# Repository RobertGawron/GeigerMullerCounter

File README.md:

# GeigerMullerCounter

## Purpose

The Geiger–Müller counter is a simple, reliable tool designed to measure ionizing radiation. It is widely used in experiments, radiation detection, and environmental monitoring.

## Principle of Operation
When a high voltage (typically 380–420V) is applied to the Geiger–Müller tube, the tube does not conduct electricity under normal conditions. However, when a radiation particle interacts with the tube, it briefly conducts a current, producing a pulse. These pulses are counted by the detector, and the number of pulses in a given time interval (typically 20 seconds to 2.5 minutes) is proportional to the level of ionizing radiation.

## Final Version
Below is an image of the device (the green PCB in the center). Other components in the image are not relevant to this project, as they belong to the [Cosmic Ray Detector](https://github.com/RobertGawron/CosmicRayDetector), where the Geiger counter is used as a building block.

## System Architecture

The diagram shows the main components and how they interact. The component IDs in parentheses match those in the circuit diagram below, making it easier to understand the circuit.

Tools: PlantUML

## Hardware 

The circuit is shown below. For a full-size image, right-click and open it in a new tab.

Tools: KiCad (for PCB design).

More info can be fond in [here](Hardware/GeigerMullerCounter/README.md).

## Software

Data from the Geiger–Müller counter is collected and managed using the [HardwareDataLogger](https://github.com/RobertGawron/HardwareDataLogger), which is built around an STM32 microcontroller for data collection, display, and storage (via SD card), and an ESP8266 for WiFi communication.

Tools: C++, Python.

## Experiments Conducted

* [Measuring Nuclear Radiation of Potassium from Cigarette Ashes](https://robertgawron.blogspot.com/2015/07/measuring-radioactivity-of-potassium.html): Cigarette ashes are the burnt remains of tobacco leaves, which are rich in potassium. In natural environments, potassium contains the radioactive isotope potassium-40 (K-40), which contributes to the measured radiation levels.
* [Cosmic Ray Detector](https://github.com/RobertGawron/CosmicRayDetector): a device designed to detect high-energy particles, known as cosmic rays, that originate from outer space.
* [Trip to Śnieżka mountain to measure radioactivity levels](https://robertgawron.blogspot.com/2015/06/a-trip-with-geiger-counter-on-sniezka.html): mountains naturally have elevated radiation levels due to increased cosmic rays and radioactive minerals in the rocks. Additionally, near Śnieżka Mountain, a Cold War-era uranium mine in Kowary contributed to the region's historical radiation levels.

## Safety Hazards

**Warning: The device operates at high voltage (380–420V). Contact with the PCB or Geiger tube while powered can cause electric shocks, injuries, or even death. Do not touch any components while the device is powered on.**

## License
This project is licensed under the MIT License. See the [LICENSE](./LICENSE) file for details.

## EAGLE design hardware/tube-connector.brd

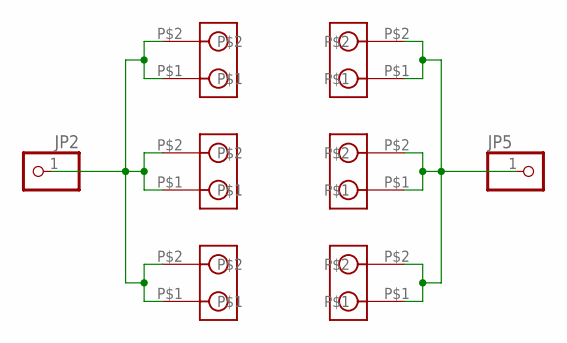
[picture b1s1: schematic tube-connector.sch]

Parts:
JP2, JP5: PINHD-1X1; 1X01
U$1, U$2, U$3, U$4, U$5, U$6: GM-CONNECTOR

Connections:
unnamed: JP2.1, U$1.P$1, U$1.P$2, U$2.P$1, U$2.P$2, U$3.P$1, U$3.P$2
unnamed: JP5.1, U$4.P$1, U$4.P$2, U$5.P$1, U$5.P$2, U$6.P$1, U$6.P$2

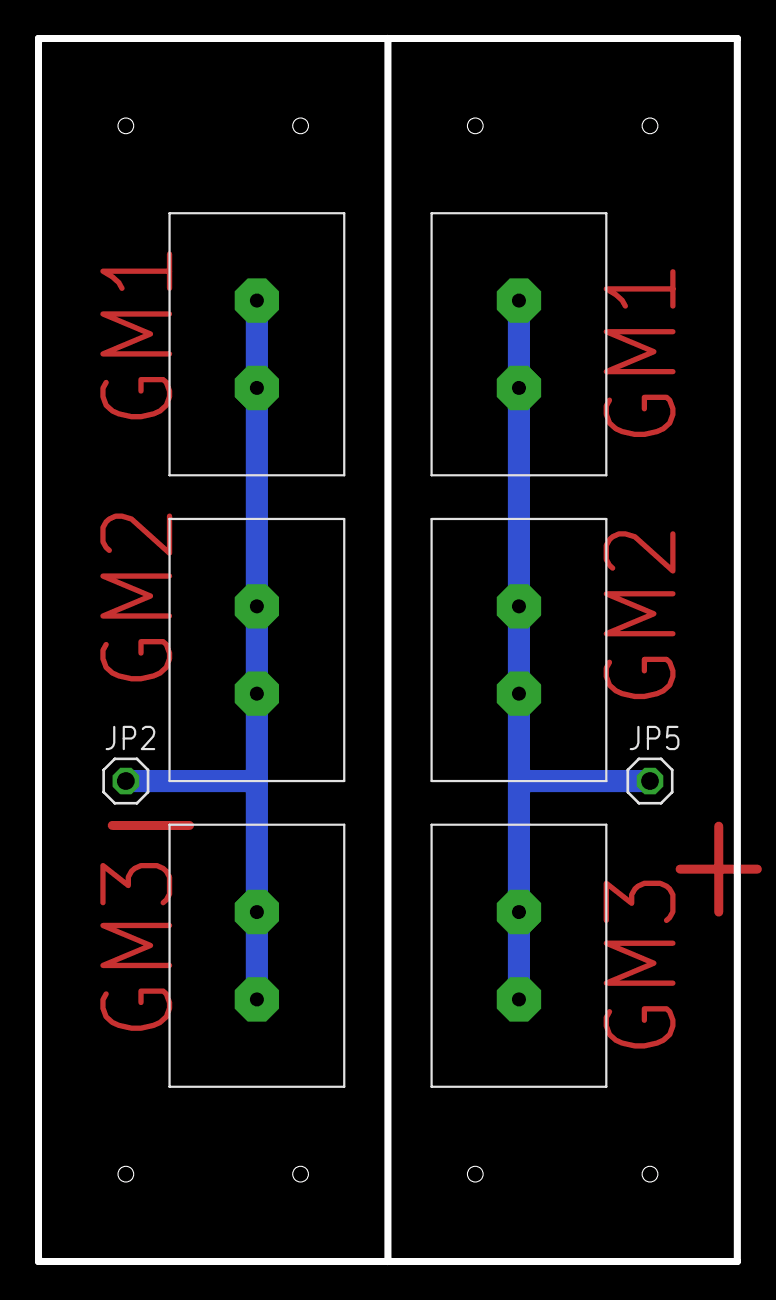
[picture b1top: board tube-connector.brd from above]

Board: 2 copper layers, 40.0 x 70.0 mm, 8 parts (0 on the bottom side), 2 nets.

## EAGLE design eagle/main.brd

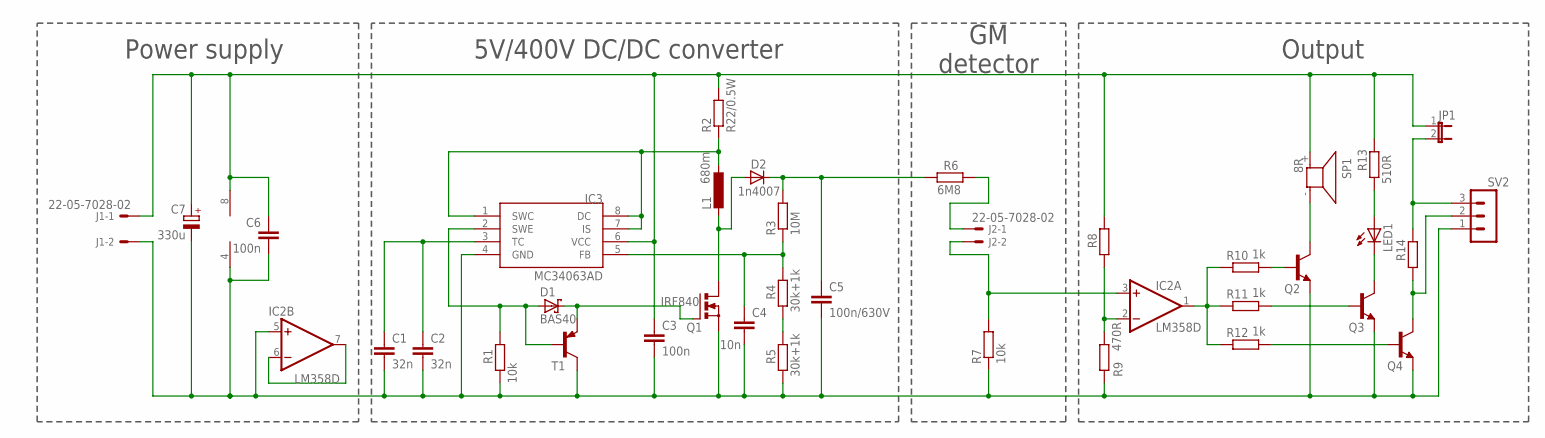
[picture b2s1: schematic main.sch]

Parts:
C1, C2: 32n; C0805
C3, C6: 100n; C0805
C4: 10n; C0805
C5: 100n/630V; C102-064X133
C7: 330u; D/7343-31R
D1: BAS40; SOT23
D2: 1n4007; DO41-10
IC2: LM358D; SO08
IC3: MC34063AD; SOIC8
J1, J2: 22-05-7028-02; 7395-02
JP1: JP1E; JP1
L1: 680m; 0207/5V
LED1: LEDSFH482; SFH482
Q1: IRF840; TO220BV
Q2, Q3, Q4: BC848ALT1SMD; SOT23
R1: 10k; R0805
R2: R22/0.5W; 0207/5V
R3: 10M; 0207/5V
R4, R5: 30k+1k; R0805
R6: 6M8; 0207/5V
R7: 10k; 0207/5V
R8: R-EU_R0805; R0805
R9: 470R; R0805
R10, R11, R12: 1k; M0805
R13: 510R; M0805
R14: R-EU_M0805; M0805
SP1: 8R; KSS1201
SV2: MA03-1
T1: BC807-40-PNP-SOT23-BEC; SOT23-BEC

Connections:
unnamed: Q4.1 (B), R12.2
unnamed: Q3.1 (B), R11.2
unnamed: LED1.K (C), Q3.3 (C)
unnamed: Q4.3 (C), R14.1, SV2.2
unnamed: C1.1, C2.1, IC3.3 (TC)
unnamed: LED1.A, R13.1
unnamed: IC3.1 (SWC), IC3.7 (IS), IC3.8 (DC), L1.1, R2.1
unnamed: IC2.1 (OUT), R10.1, R11.1, R12.1
unnamed: Q2.3 (C), SP1.- (2)
unnamed: Q2.1 (B), R10.2
unnamed: R4.1, R5.2
unnamed: C5.1, D2.C, R3.2, R6.1
unnamed: C4.1, IC3.5 (FB), R3.1, R4.2
unnamed: D1.1 (A), IC3.2 (SWE), R1.2, T1.B
unnamed: D2.A, L1.2, Q1.D
unnamed: D1.3 (C), Q1.G, T1.E
unnamed: IC2.3 (+IN), J2.2, R7.2
unnamed: J2.1, R6.2
unnamed: IC2.2 (-IN), R8.1, R9.2
unnamed: JP1.2, R14.2, SV2.3
unnamed: IC2.6 (-IN), IC2.7 (OUT)
V+: C3.1, C6.1, C7.+, IC2.8 (V+), IC3.6 (VCC), J1.1, JP1.1, R2.2, R8.2, R13.2, SP1.+ (1)
V-: C1.2, C2.2, C3.2, C4.2, C5.2, C6.2, C7.-, IC2.4 (V-), IC2.5 (+IN), IC3.4 (GND), J1.2, Q1.S, Q2.2 (E), Q3.2 (E), Q4.2 (E), R1.1, R5.1, R7.1, R9.1, SV2.1, T1.C

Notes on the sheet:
Power supply
5V/400V DC/DC converter
GM detector
Output

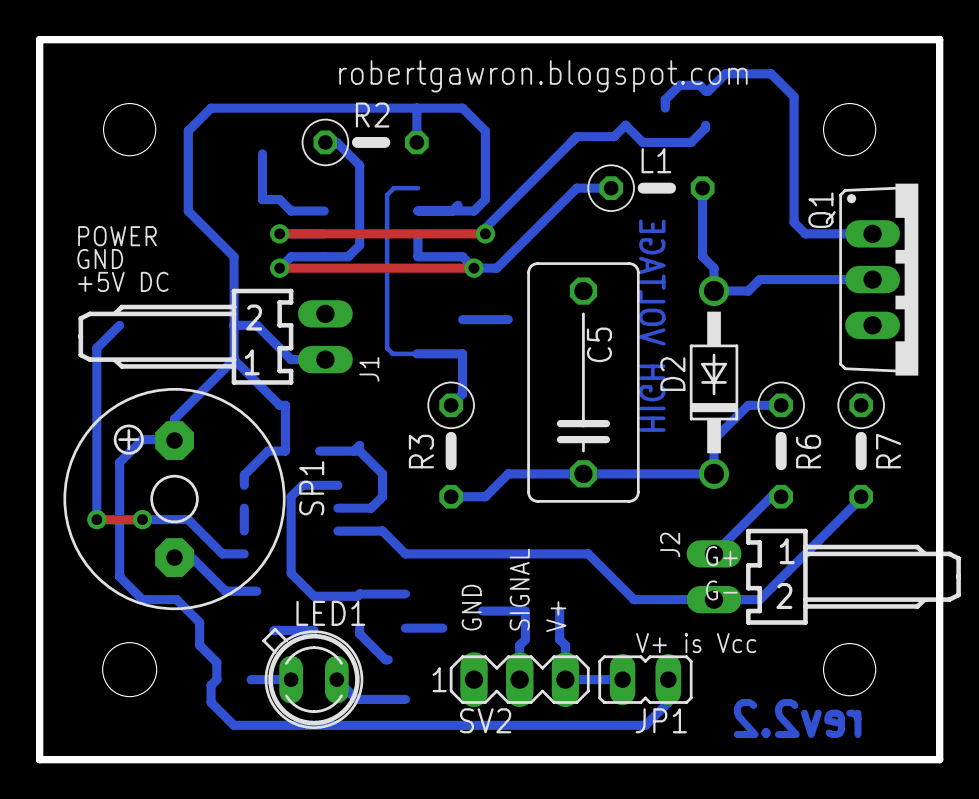
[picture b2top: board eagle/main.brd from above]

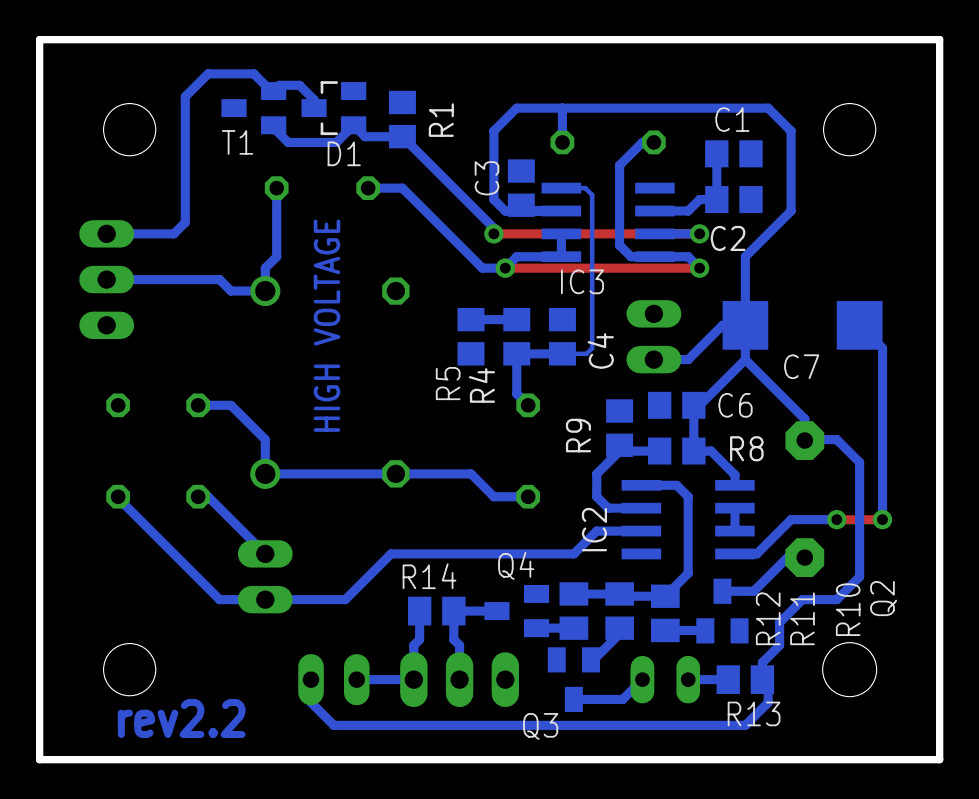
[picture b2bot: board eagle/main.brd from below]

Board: 2 copper layers, 50.0 x 40.0 mm, 37 parts (23 on the bottom side), 23 nets.

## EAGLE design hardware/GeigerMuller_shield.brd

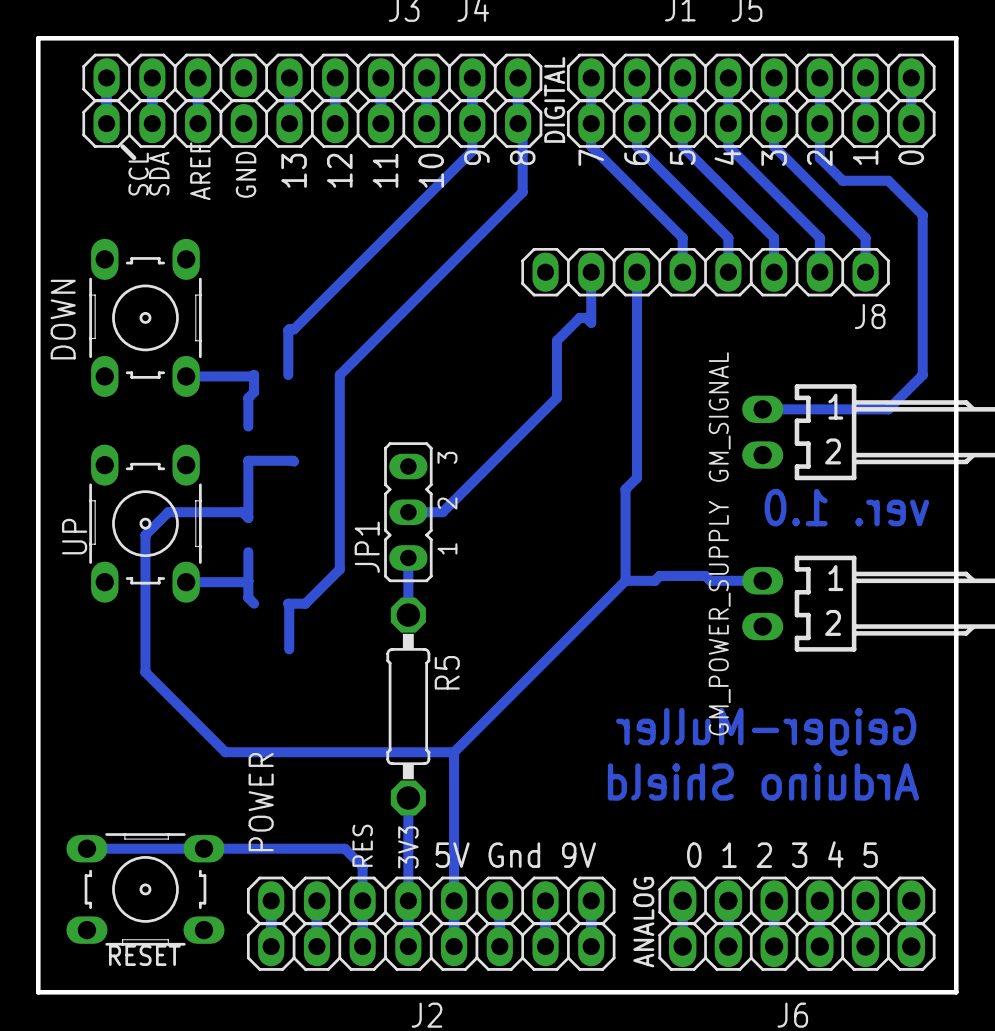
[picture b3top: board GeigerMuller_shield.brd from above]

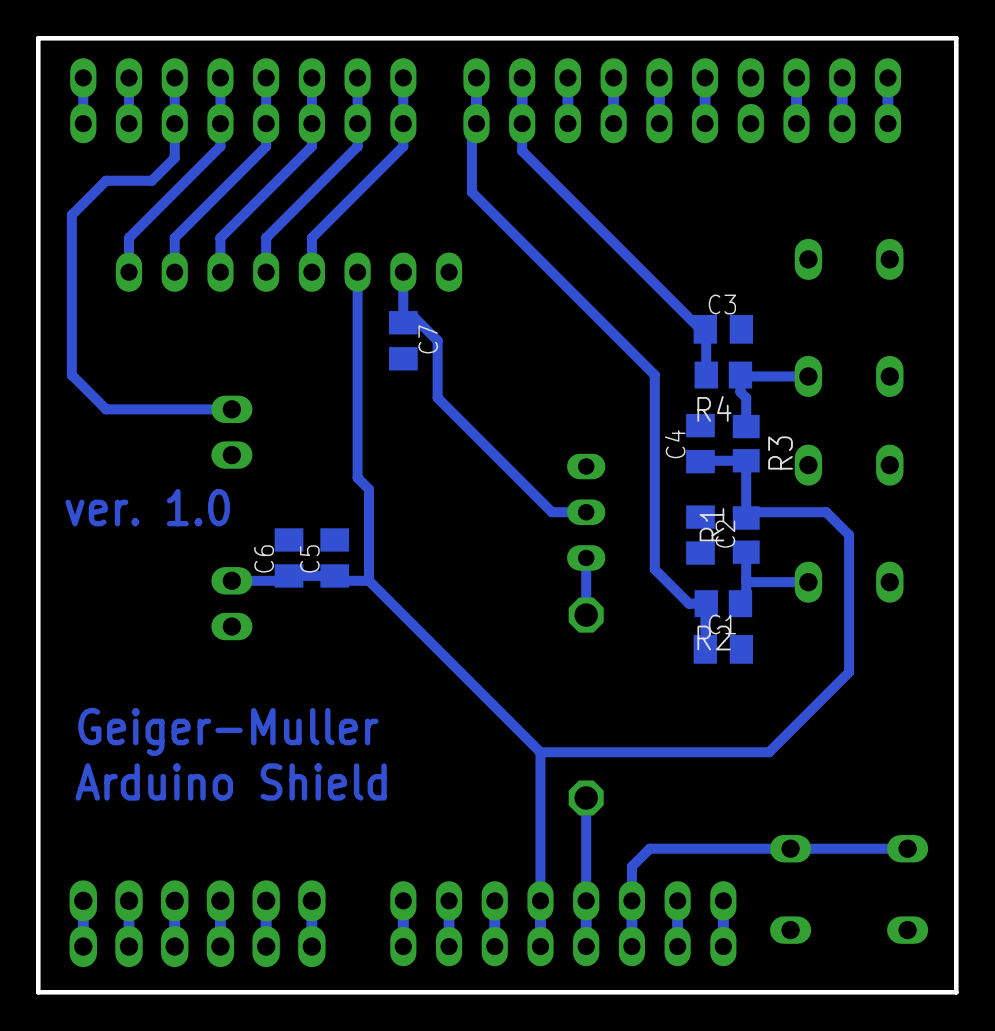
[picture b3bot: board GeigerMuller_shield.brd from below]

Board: 2 copper layers, 51.0 x 53.0 mm, 28 parts (11 on the bottom side), 34 nets.

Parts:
ANALOG: 1X06
C1, C3, C5, C6, C7: 10n; C0805K
C2, C4: 100n; C0805K
DOWN: B3F-10XX
GM_POWER_SUPPLY: 22-05-7028-02; 7395-02
GM_SIGNAL: 22-05-7028-02; 7395-02
J1, J2, J5, J8: 1X08-TH
J3, J4: 1X10-TH
J6: 1X06
JP1: JP2
POWER: 1X08-TH
R1, R3: 10k; R0805
R2, R4: 1k; R0805
R5: 220R; 0207/10
RESET: B3F-10XX
U$1: DISCLAIMER
UP: B3F-10XX

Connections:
3V3: J2.4, POWER.4, R5.2
+5V: C2.1, C4.1, C5.1, C6.1, GM_POWER_SUPPLY.1, J2.5, J8.6, POWER.5, R1.2, R3.2
+9V: J2.8, POWER.8
BUTTON_1: C1.1, J3.1, J4.1, R2.2
BUTTON_2: C3.1, J3.2, J4.2, R4.2
GM_SIGNAL: GM_SIGNAL.1, J1.3, J5.3
GND: C1.2, C2.2, C3.2, C4.2, C5.2, C6.2, C7.2, DOWN.4, GM_POWER_SUPPLY.2, GM_SIGNAL.2, J2.6, J2.7, J3.7, J4.7, J8.8, POWER.6, POWER.7, RESET.1, RESET.2, UP.4
LCD_BACKLIGHT: C7.1, J8.7, JP1.2
LCD_CS: J1.7, J5.7, J8.4
LCD_DC: J1.6, J5.6, J8.3
LCD_DIN: J1.5, J5.5, J8.2
LCD_RST: J1.8, J5.8, J8.5
LCD_SCLK: J1.4, J5.4, J8.1
unnamed: J3.6, J4.6
unnamed: J1.2, J5.2
unnamed: J3.4, J4.4
unnamed: J3.5, J4.5
unnamed: R1.1, R2.1, UP.2
unnamed: J1.1, J5.1
unnamed: J3.3, J4.3
unnamed: JP1.1, R5.1
unnamed: DOWN.2, R3.1, R4.1
unnamed: ANALOG.1, J6.1
unnamed: ANALOG.2, J6.2
unnamed: ANALOG.3, J6.3
unnamed: ANALOG.4, J6.4
unnamed: ANALOG.5, J6.5
unnamed: ANALOG.6, J6.6
unnamed: J2.2, POWER.2
unnamed: J2.1, POWER.1
unnamed: J3.9, J4.9
unnamed: J3.10, J4.10
unnamed: J3.8, J4.8
RESET: J2.3, POWER.3, RESET.3, RESET.4

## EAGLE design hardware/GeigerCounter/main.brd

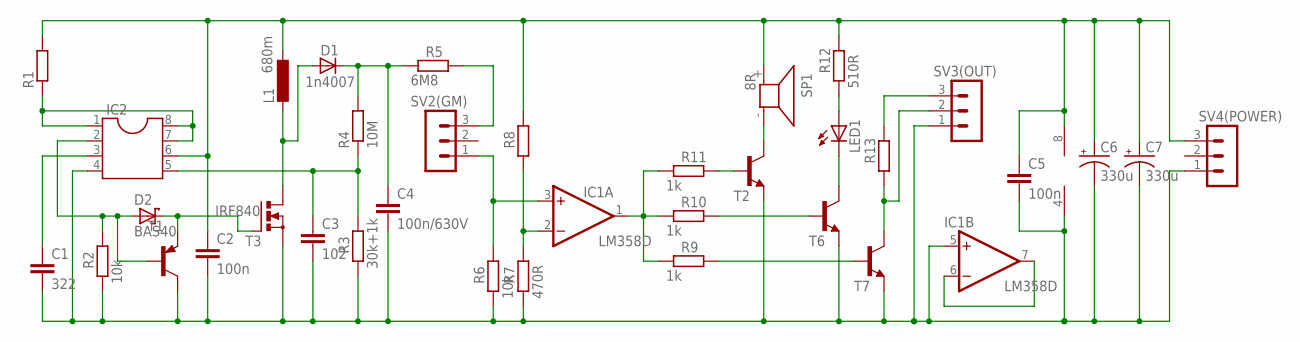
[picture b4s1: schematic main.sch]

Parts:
C1: 322; C050-025X075
C2, C5: 100n; C3216
C3: 102; C050-025X075
C4: 100n/630V; C102-064X133
C6, C7: 330u; A/3216-18W
D1: 1n4007; DO41-10
D2: BAS40; SOT23
IC1: LM358D; SO08
IC2: DIL8; DIL08
L1: 680m; 0207/5V
LED1: LEDSFH482; SFH482
R1, R8: R-EU_0207/5V; 0207/5V
R2, R6: 10k; 0207/5V
R3: 30k+1k; 0207/5V
R4: 10M; 0207/5V
R5: 6M8; 0207/12
R7: 470R; 0207/5V
R9, R10, R11: 1k; M1206
R12: 510R; M1206
R13: R-EU_M1206; M1206
SP1: 8R; KSS1201
SV2(GM), SV3(OUT), SV4(POWER): MA03-1
T1: BC807-40-PNP-SOT23-BEC; SOT23-BEC
T2, T6, T7: BC848ALT1SMD; SOT23
T3: IRF840; TO220BV

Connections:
unnamed: R9.2, T7.1 (B)
unnamed: R10.2, T6.1 (B)
unnamed: LED1.K (C), T6.3 (C)
unnamed: R13.1, SV3(OUT).2, T7.3 (C)
unnamed: C1.1, IC2.3
unnamed: LED1.A, R12.1
unnamed: IC1.1 (OUT), R9.1, R10.1, R11.1
unnamed: SP1.- (2), T2.3 (C)
unnamed: R11.2, T2.1 (B)
unnamed: IC2.1, IC2.7, IC2.8, R1.1
unnamed: C4.1, D1.C, R4.2, R5.1
unnamed: C3.1, IC2.5, R3.2, R4.1
unnamed: D2.1 (A), IC2.2, R2.2, T1.B
unnamed: D1.A, L1.2, T3.D
unnamed: D2.3 (C), T1.E, T3.G
unnamed: IC1.3 (+IN), R6.2, SV2(GM).1
unnamed: IC1.2 (-IN), R7.2, R8.1
unnamed: R5.2, SV2(GM).3
unnamed: R13.2, SV3(OUT).3
unnamed: IC1.6 (-IN), IC1.7 (OUT)
V+: C2.1, C5.1, C6.+, C7.+, IC1.8 (V+), IC2.6, L1.1, R1.2, R8.2, R12.2, SP1.+ (1), SV4(POWER).3
V-: C1.2, C2.2, C3.2, C4.2, C5.2, C6.-, C7.-, IC1.4 (V-), IC1.5 (+IN), IC2.4, R2.1, R3.1, R6.1, R7.1, SV3(OUT).1, SV4(POWER).1, T1.C, T2.2 (E), T3.S, T6.2 (E), T7.2 (E)

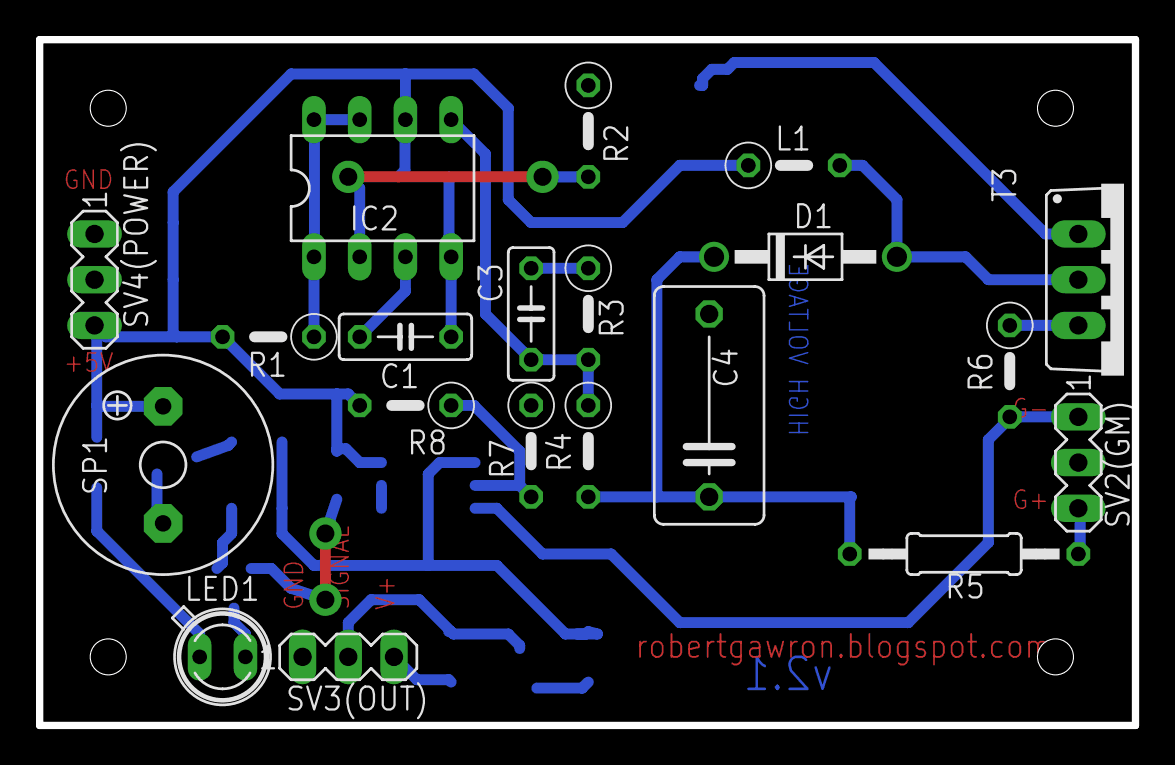
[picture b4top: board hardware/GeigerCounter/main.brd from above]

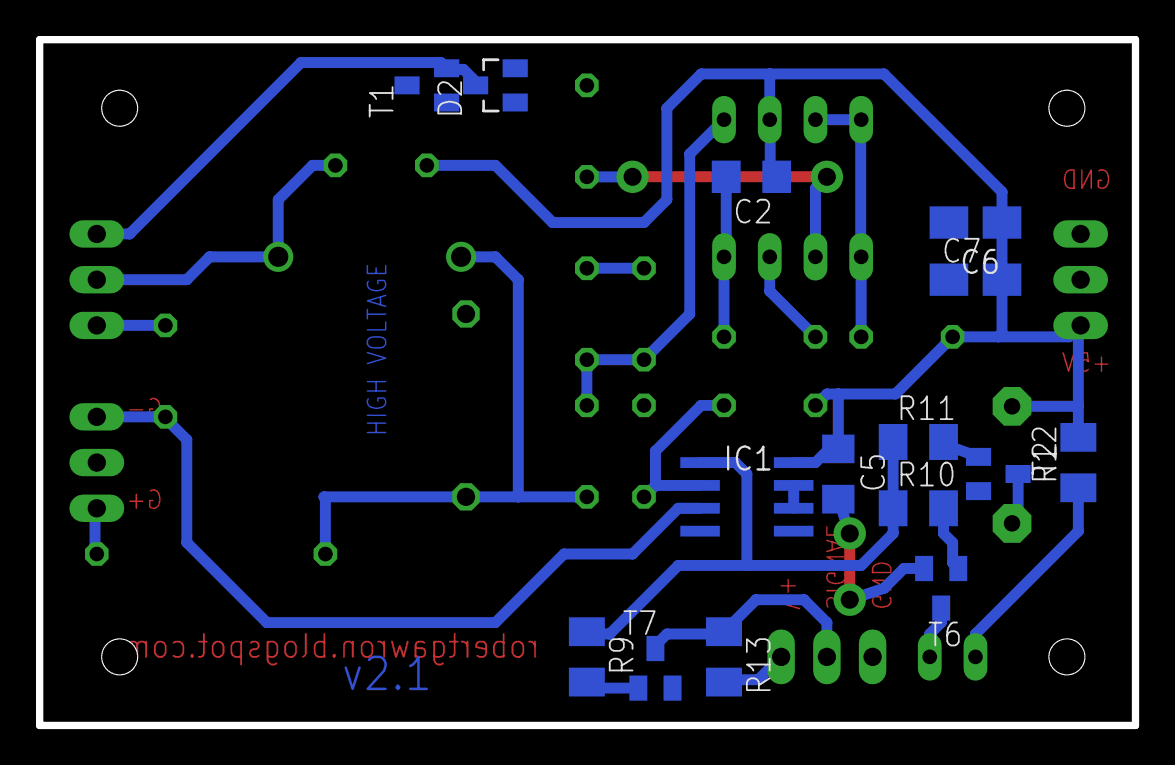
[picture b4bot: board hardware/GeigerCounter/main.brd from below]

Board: 2 copper layers, 60.9 x 38.1 mm, 35 parts (15 on the bottom side), 22 nets.

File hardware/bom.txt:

Partlist exported from C:/Users/rgawron/GeigerMullerCounter/hardware/main.sch at 2015-07-04 11:56:20

Part       Value     Device                 Package      Description                          MF MPN OC_FARNELL OC_NEWARK
C1         32n       C-EU050-025X075        C050-025X075 CAPACITOR, European symbol                                      
C2         100n      C-EUC3216              C3216        CAPACITOR, European symbol                                      
C3         10n       C-EU050-025X075        C050-025X075 CAPACITOR, European symbol                                      
C4         100n/630V C-EU102-064X133        C102-064X133 CAPACITOR, European symbol                                      
C5         100n      C-EUC3216              C3216        CAPACITOR, European symbol                                      
C6         330u      CPOL-USA/3216-18W      A/3216-18W   POLARIZED CAPACITOR, American symbol                            
C7         330u      CPOL-USA/3216-18W      A/3216-18W   POLARIZED CAPACITOR, American symbol                            
D1         1n4007    1N4004                 DO41-10      DIODE                                                           
D2         BAS40     BAS40                  SOT23        Silicon Schottky Diodes                                         
IC1        LM358D    LM358D                 SO08         OP AMP also LM158; LM258; LM2904                                
IC2        MC34063   DIL8                   DIL08        Dual In Line / Socket                                           
L1         680m      L-EU0207/5V            0207/5V      INDUCTOR, European symbol                                       
LED1                 LEDSFH482              SFH482       LED                                                             
R1         R22/0.5W  R-EU_0207/5V           0207/5V      RESISTOR, European symbol                                       
R2         10k       R-EU_R1206             R1206        RESISTOR, European symbol                                       
R3         30k+1k    R-EU_0207/5V           0207/5V      RESISTOR, European symbol                                       
R4         10M       R-EU_0207/5V           0207/5V      RESISTOR, European symbol                                       
R5         6M8       R-EU_0207/12           0207/12      RESISTOR, European symbol                                       
R6         10k       R-EU_0207/5V           0207/5V      RESISTOR, European symbol                                       
R7         470R      R-EU_0207/5V           0207/5V      RESISTOR, European symbol                                       
R8                   R-EU_R1206             R1206        RESISTOR, European symbol                                       
R9         1k        R-EU_M1206             M1206        RESISTOR, European symbol                                       
R10        1k        R-EU_M1206             M1206        RESISTOR, European symbol                                       
R11        1k        R-EU_M1206             M1206        RESISTOR, European symbol                                       
R12        510R      R-EU_M1206             M1206        RESISTOR, European symbol                                       
R13                  R-EU_M1206             M1206        RESISTOR, European symbol                                       
SP1        8R        KSS1201                KSS1201      SPEAKER                                     unknown    unknown  
SV2(GM)              MA03-1                 MA03-1       PIN HEADER                                  unknown    unknown  
SV3(OUT)             MA03-1                 MA03-1       PIN HEADER                                  unknown    unknown  
SV4(POWER)           MA03-1                 MA03-1       PIN HEADER                                  unknown    unknown  
T1                   BC807-40-PNP-SOT23-BEC SOT23-BEC    PNP Transistror                                                 
T2                   BC848ALT1SMD           SOT23        NPN Transistor                                                  
T3         IRF840    BUZ11BV                TO220BV      N-CHANNEL MOS FET                                               
T6                   BC848ALT1SMD           SOT23        NPN Transistor                                                  
T7                   BC848ALT1SMD           SOT23        NPN Transistor

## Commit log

2014-06-13 Morged stuff from my other project ( https://github.com/RobertGawron/ArduinoAnts )
2014-12-21 IAR implementation removed.
2014-12-21 Empty CooCox project.
2014-12-21 Removed unused files.
2014-12-21 Possible to display messages on LCD.
2014-12-21 Dummy data presented on LCD.
2014-12-21 Code formating.
2014-12-21 Touch LCD sensor added.
2014-12-21 Added drawing a simple graph.
2014-12-22 Draft of layout manager.
2014-12-22 Files renamed, methods names changed.
2014-12-22 Files rename.
2014-12-22 Added #ifndef #define #endif trinity.
2014-12-22 Added #ifndef ... trinity, code cleanup.
2014-12-23 Added layout generated specific files.
2014-12-23 Added real intro layout.
2014-12-26 Stub for temperature sensor.
2014-12-26 Draft of temperature sensor (reading from GPIO).
2014-12-26 Types from inttypes.h used everywhere.
2015-04-04 HW project added. Directory structure changed.
2015-04-04 Fixed directory structure.
2015-04-04 Removed unused code.
2015-04-04 Fixed project name.
2015-04-04 Fixed description of the project.
2015-04-04 Removed touch sensor code.
2015-04-04 Working version.
2015-04-04 Fixed PCB.
2015-05-27 Version with new step-up driver.
2015-06-14 Built and tested version.
2015-06-14 Tested version.
2015-06-14 Fixed as is on HW model.
2015-06-17 LCD and GPIO code moved to separate files.
2015-06-17 Indentation fixed.
2015-06-18 Folder structure changed.
2015-06-18 Software relase v1.0
2015-06-18 HW version 2.2
2015-06-28 Extended directory structure.
2015-06-28 Project structure modification.
2015-06-28 Fixed uppercase in directory name.
2015-06-28 Added README.
2015-06-28 Added PC visualization of received data.
2015-07-01 Counts handling moved to new .h/.c files.
2015-07-01 Added missing changes.
2015-07-04 Issue #4 fixed.
2015-07-04 Feature #1 in progress.
2015-07-04 Refactoring for #1.
2015-07-05 Refactoring needed for #1 in progress.
2015-07-05 Further refactoring needed for #1.
2015-07-05 Final version of the refactoring for #1
2015-07-05 Feature #1 resolve.
2015-07-05 Issue #11 fixed.
2015-07-05 Issue #8 fixed.
2015-07-13 PCB for GM connectors.
2015-07-13 Top description layer added.
2015-07-13 Fixed bug in displaying results.
2015-07-15 After first prototype.
2015-07-29 P-Star 25K50 Micro peoject added.
2015-07-29 P-Star25K50 Micr: added missing files.
2015-07-29 Project structure update.
2015-07-29 README updated by project setup howto.
2015-07-29 USB drivers added.
2016-07-24 Removed obsolete fimware.
2016-07-24 Arduino software version.
2016-07-24 Removed pointless files.
2016-07-24 Fixing dir structure.
2016-07-24 Fixinf dir structure part 2.
2016-08-16 Changed LCD pins.
2016-08-16 Arduino shield added.
2016-08-16 Fixed resistor value.
2016-08-16 Histogram bins fix.
2016-08-16 Bin counting fix.
2016-08-16 Debouncing works a bit better.
2016-08-26 Fixed key handling. Extended Welcome Layout.
2016-08-26 Fixed switching between layouts.
2016-08-26 removed whitespaces.
2016-08-26 Primitive implementation of uSv/h dosage.
2016-08-26 Fixed uSv/h conversion.
2016-08-27 Historgram and cpm to uSv/h fixes.
2017-01-08 Fixes in arduino shield.
2018-05-27 PCB is now fixed.
2018-09-09 local libraries added
2018-09-09 moved to eclipse
2018-09-09 fixed project structure
2018-09-13 keyboard support
2018-09-13 remove impl of Layout class
2018-09-13 draft of layouts stuff
2018-09-13 draft of pulse layout
2018-09-13 cleanup
2018-09-13 fix in sample buffer
2018-09-13 class rename
2018-09-13 split function
2018-09-13 default constructors
2018-09-13 class to handle layouts
2018-09-13 impl of layout handler class
2018-09-13 refactor how measurements are stored
2018-09-13 method variable name refactor
2018-09-13 class name change
2018-09-13 class splited to a sparate file
2018-09-13 comments
2018-09-13 whitespace
2018-09-14 implementation of the buffer
2018-09-14 infinitive loop for event handling
2018-09-15 fixed circular buffer
2018-09-15 remove arduino ide based project
2018-09-15 directory rename
2018-09-15 fixed footprint place
2018-09-19 folder for eagle version
2018-09-19 kicad version of main pcb
2018-09-19 Create LICENSE
2018-09-19 component placement fix
2018-09-19 add missing gerber file
2018-09-19 even more missing files added
2018-09-19 elements placement fix
2018-09-19 drc check ok
2018-09-20 directory structure change
2019-02-16 draft for the stm32 firmware
2019-02-16 new hw ready to be send to pcb company
2019-02-16 folder structure cleanup
2019-02-17 remove obsolete kicad projects
2019-02-17 fixes after hw tests
2019-03-24 warnings threated as errors
2019-03-24 fixed index error
2019-03-24 label to display dosage
2019-03-24 fixed extern
2019-03-24 added serial port files
2019-03-24 com port moved to sparate file
2019-06-04 removed junk files, added gitignore
2019-06-04 removed cache reference
2019-06-04 removed gm connector and arduino projects
2019-06-08 cleaned up include structure
2019-06-16 sw from my old arduino project as a draft
2019-06-16 working arduino sw firmware
2019-06-16 pcb for gm counter, gm tube connector and arduino
2019-06-16 refactored code
2019-06-16 moved from eagle to kicad
2019-06-16 stm32 fimware
2019-06-16 added more detailed readme
2019-08-11 unified with my other repositories
2019-08-11 architecture documents
2019-08-11 remove junk text
2019-08-11 fix label place
2019-08-11 added warning about hv
2019-08-11 champter rename
2019-08-11 travis to check latex generation
2019-08-11 add CI status
2019-08-11 fixed formatting
2020-06-06 use kicad elments (after eagle to kicad transition)
2020-09-12 add suport for vscode build
2020-09-12 add makefile
2020-09-12 update of cubemx project
2020-09-12 possible to compile and flash, not posssible to debug, or use vscode key bindings
2020-09-13 add bindings for build and flashing, note: this file must be copied to C:\Users\USER_NAME\AppData\Roaming\Code\User\keybindings.json and is shared between all projects
2020-10-09 draft + working timer
2020-10-09 added logger
2020-10-09 add circular buffer
2020-10-09 add display logic (no hw implementation)
2020-10-09 add display hw impolementation and meassurement calculator
2020-10-09 add missing component initialization
2020-10-09 code cleanup
2020-10-09 remove project for older board version
2020-10-10 fixed logger timer to 60s
2020-10-10 split hw and application logic of logger
2020-10-10 add extra compilation warning flags, not all are possible to be enabled as errors due to implementation of HAL and LCD library (that I don't want to modify)
2020-10-10 Squashed 'Test/UnitTest/UTestLib/' content from commit 9e4f32de
    git-subtree-dir: Test/UnitTest/UTestLib
    git-subtree-split: 9e4f32de20710bff2ad0b6dd70e9ae14fbe16c11
2020-10-10 add dummmy tests
2020-10-11 basic tests structure
2020-10-11 part of unit tests for GMCircularBuffer_GetElement
2020-10-12 fixed args order
2020-10-12 firmware can be now compiled to .exe
2020-10-12 add python bindings
2020-10-13 add draft of gui for simulator
2020-10-13 add draft of hw display simulation
2020-10-14 hw display implementation
2020-10-15 fully working versionr
2020-10-15 remove files moved to new repo
2020-10-15 Squashed 'Software/Firmware/' content from commit 37d90c36
    git-subtree-dir: Software/Firmware
    git-subtree-split: 37d90c36ef6dff2428dff3a75682a6a990aea3fe
2020-10-15 cleanup after moving firmware to separate repo
2020-10-17 remove old version
2020-10-17 Squashed 'Software/HardwareDataLogger/' content from commit 36e64a0b
    git-subtree-dir: Software/HardwareDataLogger
    git-subtree-split: 36e64a0b74689bc3145da8180f2f13aac98a8adf
2020-10-23 move from travis to github actions, move ,gitignore for Kicad files into hardware directory
2020-10-23 link build status to project's build section
2020-10-24 move (for diagrams) from .png to .svg
2020-10-24 move (for diagrams) from .png to .svg - add missing .svg file
2020-10-24 Squashed 'Software/HardwareDataLogger/' changes from 36e64a0b..dc3c36eb
    dc3c36eb Merge pull request #21 from RobertGawron/develop
    a8342c6a Merge pull request #20 from RobertGawron/feature/add_contionous_integration
    304d8cda fix c linter issues
    4a7e1a6d Merge pull request #19 from RobertGawron/develop
    1880f227 Merge pull request #18 from RobertGawron/feature/add_contionous_integration
    7c2c33d9 exclude external libs from repo programming language statistics
2020-11-06 Add info about zener diode voltage (#89)
2020-11-06 Fix grammar mistakes (found by Code Spell Checker add-on in VSCode). (fix #100)
2020-11-06 Squashed 'Software/HardwareDataLogger/' changes from dc3c36eb..58e2b477
    58e2b477 Merge pull request #24 from RobertGawron/develop
    74d71741 Merge pull request #23 from RobertGawron/fix/remove_gammar_mistakes
    8752828e Fix grammar mistakes (found by Code Spell Checker add-on in VSCode). (fix #22)
    git-subtree-dir: Software/HardwareDataLogger
    git-subtree-split: 58e2b477f2824c01ec6d98d952829f0472e2d4a0
2024-09-09 add image of the device and fix url in readme
2024-09-13 hw revision 2.3
